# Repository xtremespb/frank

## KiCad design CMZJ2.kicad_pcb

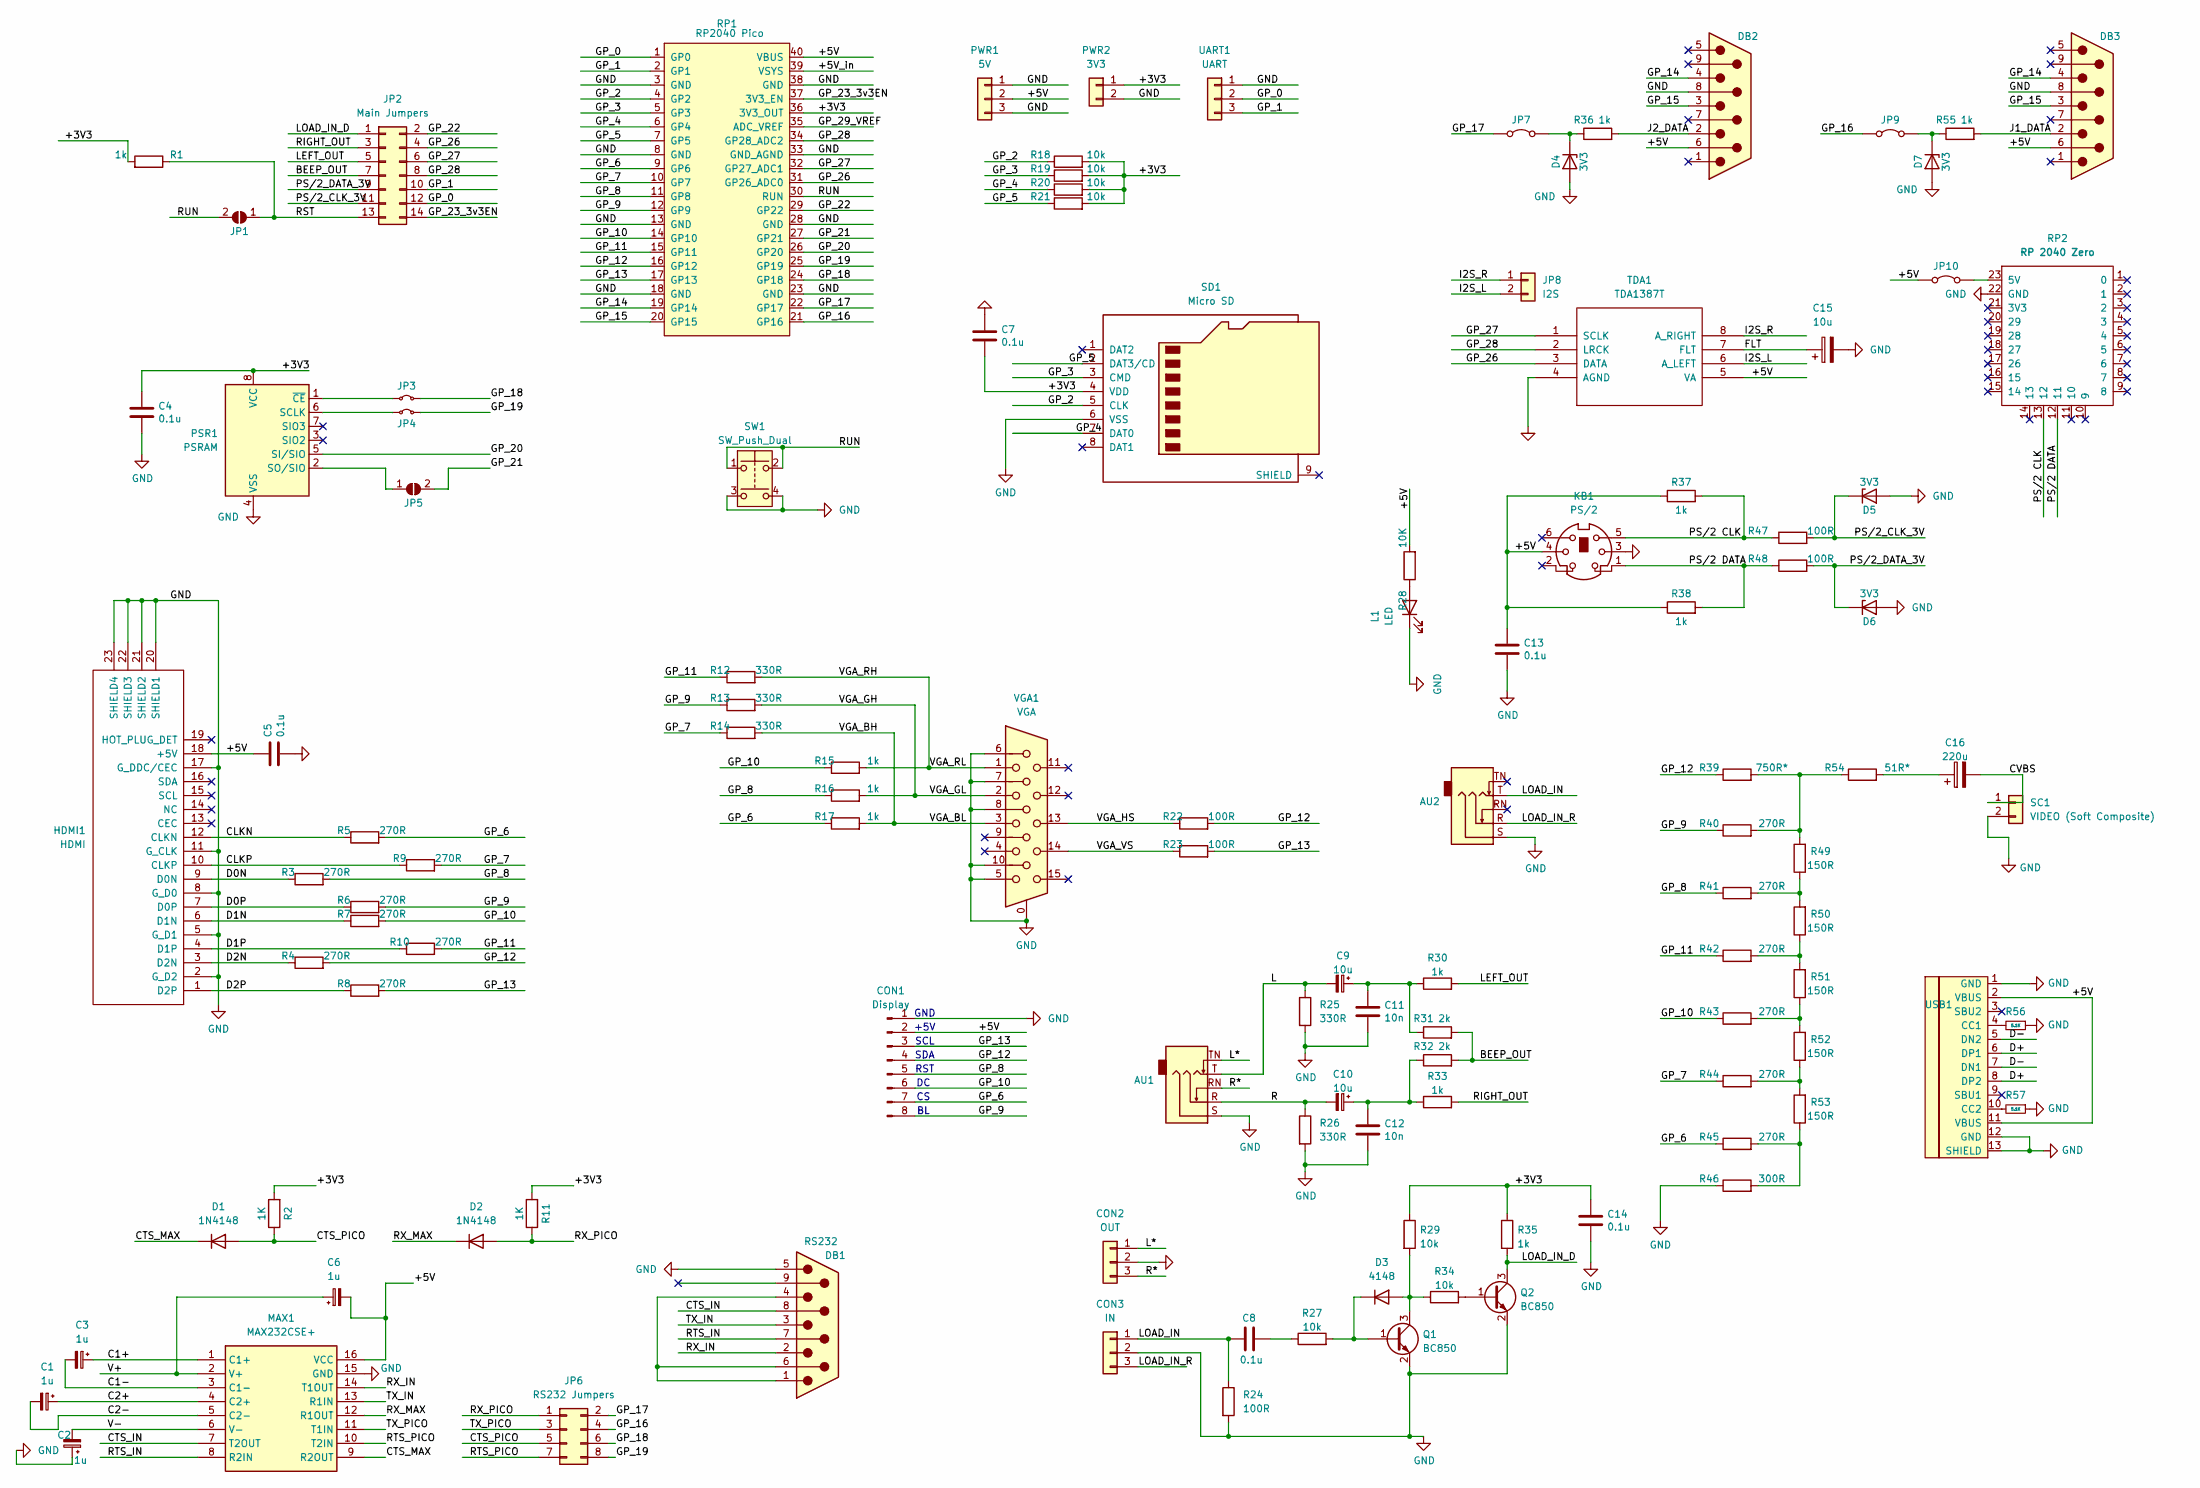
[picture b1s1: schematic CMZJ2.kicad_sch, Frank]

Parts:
AU1: AUDIO OUT; Medved_Jack_3.5mm_CUI_SJ1-3535NG_Horizontal
AU2: AUDIO IN; Medved_Jack_3.5mm_CUI_SJ1-3535NG_Horizontal
C1, C2, C3, C6: 1u; Medved_CP_Radial_D5.0mm_P2.50mm
C4, C5, C7, C8, C13, C14: 0.1u; C_0805_2012Metric_Pad1.18x1.45mm_HandSolder
C9, C10, C15: 10u; Medved_CP_Radial_D5.0mm_P2.50mm
C11, C12: 10n; C_0805_2012Metric_Pad1.18x1.45mm_HandSolder
C16: 220u; Medved_CP_Radial_D5.0mm_P2.50mm
CON1: Display; Medved_PinHeader_1x08_P2.54mm_Vertical
CON2: OUT; Medved_Pins_1x03_P2.54mm_Vertical_GM
CON3: IN; Medved_Pins_1x03_P2.54mm_Vertical_GM
D1, D2: 1N4148; R_0805_PLUS
D3: 4148; R_0805_PLUS
D4, D5, D6, D7: 3V3; R_0805_PLUS
DB1: RS232; DSUB-9_Joystick
DB2, DB3: Joystick; DSUB-9_Joystick
HDMI1: HDMI
JP1: JMP RUN; SolderJumper-2_P1.3mm_Open_RoundedPad1.0x1.5mm
JP2: Main Jumpers; Medved_PinHeader_2x07_P2.54mm_Vertical
JP3: GP18 Jumper; Medved_PinHeader_1x02_P2.54mm_Vertical_R
JP4: GP19 Jumper; Medved_PinHeader_1x02_P2.54mm_Vertical_R
JP5: JMP PSRAM; SolderJumper-2_P1.3mm_Open_RoundedPad1.0x1.5mm
JP6: RS232 Jumpers; Medved_PinHeader_2x04_P2.54mm_Vertical
JP7, JP9, JP10: RP ZERO +5V Jumper; Medved_PinHeader_1x02_P2.54mm_Vertical_R
JP8: I2S; Medved_PinHeader_1x02_P2.54mm_Vertical_NoLB
KB1: PS/2; Connector_Mini-DIN_Female_6Pin_2rows
L1: LED; LED_0805_2012Metric_Pad1.15x1.40mm_HandSolder
MAX1: MAX232CSE+; SOIC127P600X175-16N; Mouser Part Number 700-MAX232CSE
PSR1: PSRAM; SO-8_5.3x6.2mm_P1.27mm
PWR1: 5V; Medved_Pins_1x03_P2.54mm_Vertical
PWR2: 3V3; Medved_PinHeader_1x02_P2.54mm_Vertical
Q1, Q2: BC850; SOT-23_PLUS2
R1, R15, R16, R17, R30, R33, R35, R36, R37, R38, R55: 1k; R_0805_2012Metric_Pad1.20x1.40mm_HandSolder
R2, R11: 1K; R_0805_2012Metric_Pad1.20x1.40mm_HandSolder
R3, R4, R5, R6, R7, R8, R9, R10, R40, R41, R42, R43, R44, R45: 270R; R_0805_2012Metric_Pad1.20x1.40mm_HandSolder
R12, R13, R14, R25, R26: 330R; R_0805_2012Metric_Pad1.20x1.40mm_HandSolder
R18, R19, R20, R21, R27, R29, R34: 10k; R_0805_2012Metric_Pad1.20x1.40mm_HandSolder
R22, R23, R24, R47, R48: 100R; R_0805_2012Metric_Pad1.20x1.40mm_HandSolder
R28: 10K; R_0805_2012Metric_Pad1.20x1.40mm_HandSolder
R31, R32: 2k; R_0805_2012Metric_Pad1.20x1.40mm_HandSolder
R39: 750R*; R_0805_2012Metric_Pad1.20x1.40mm_HandSolder
R46: 300R; R_0805_2012Metric_Pad1.20x1.40mm_HandSolder
R49, R50, R51, R52, R53: 150R; R_0805_2012Metric_Pad1.20x1.40mm_HandSolder
R54: 51R*; R_0805_2012Metric_Pad1.20x1.40mm_HandSolder
R56, R57: 5.1K; R_0805_2012Metric_Pad1.20x1.40mm_HandSolder
RP1: RP2040 Pico; Raspberry_Pi_Pico_SMT_THT_MOD_2
RP2: RP 2040 Zero; rp2040-zero-tht
SC1: VIDEO (Soft Composite); AV_MOD_III-8.4-5
SD1: Micro SD; Medved_SD_Card
SW1: SW_Push_Dual; Button_SMD_3x3x2
TDA1: TDA1387T; SO-8_5.3x6.2mm_P1.27mm
UART1: UART; Medved_Pins_1x03_P2.54mm_Vertical
USB1: USB Type C; USB-TYPE-C-31-M-12_lib2; LCSC C165948
VGA1: VGA; Medved_DSUB-15-HD_Female_Horizontal

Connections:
/+3V3: C4.1, C7.2, C14.1, PSR1.8 (VCC), PWR2.1, R1.2, R2.2, R11.2, R18.2, R19.2, R20.2, R21.2, R29.1, R35.1, RP1.36 (3V3_OUT), SD1.4 (VDD)
/+5V: C5.1, C6.2, C13.1, CON1.2, DB2.6, DB3.6, HDMI1.18 (+5V), JP10.1 (A), KB1.4, MAX1.16 (VCC), PWR1.2, R28.2, R37.1, R38.1, RP1.40 (VBUS), TDA1.5 (VA), USB1.2 (VBUS), USB1.11 (VBUS)
/+5V_in: RP1.39 (VSYS)
/BEEP_OUT: JP2.7, R31.2, R32.2
/C1+: C3.1, MAX1.1 (C1+)
/C1-: C3.2, MAX1.3 (C1-)
/C2+: C1.1, MAX1.4 (C2+)
/C2-: C1.2, MAX1.5 (C2-)
/CLKN: HDMI1.12 (CLKN), R5.1
/CLKP: HDMI1.10 (CLKP), R9.1
/CTS_MAX: D1.1 (K), MAX1.9 (R2OUT)
/CTS_PICO: D1.2 (A), JP6.5, R2.1
/CVBS: C16.2, SC1.1
/D0N: HDMI1.9 (D0N), R3.1
/D0P: HDMI1.7 (D0P), R6.1
/D1N: HDMI1.6 (D1N), R7.1
/D1P: HDMI1.4 (D1P), R10.1
/D2N: HDMI1.3 (D2N), R4.1
/D2P: HDMI1.1 (D2P), R8.1
/D+: USB1.6 (DP1), USB1.8 (DP2)
/D-: USB1.5 (DN2), USB1.7 (DN1)
/FLT: C15.1, TDA1.7 (FLT)
/GP_0: JP2.12, RP1.1 (GP0), UART1.2
/GP_1: JP2.10, RP1.2 (GP1), UART1.3
/GP_2: R18.1, RP1.4 (GP2), SD1.5 (CLK)
/GP_3: R19.1, RP1.5 (GP3), SD1.3 (CMD)
/GP_4: R20.1, RP1.6 (GP4), SD1.7 (DAT0)
/GP_5: R21.1, RP1.7 (GP5), SD1.2 (DAT3/CD)
/GP_6: CON1.7, R5.2, R17.1, R45.1, RP1.9 (GP6)
/GP_7: R9.2, R14.1, R44.1, RP1.10 (GP7)
/GP_8: CON1.5, R3.2, R16.1, R41.1, RP1.11 (GP8)
/GP_9: CON1.8, R6.2, R13.1, R40.1, RP1.12 (GP9)
/GP_10: CON1.6, R7.2, R15.1, R43.1, RP1.14 (GP10)
/GP_11: R10.2, R12.1, R42.1, RP1.15 (GP11)
/GP_12: CON1.4, R4.2, R22.2, R39.1, RP1.16 (GP12)
/GP_13: CON1.3, R8.2, R23.2, RP1.17 (GP13)
/GP_14: DB2.4, DB3.4, RP1.19 (GP14)
/GP_15: DB2.3, DB3.3, RP1.20 (GP15)
/GP_16: JP6.4, JP9.1 (A), RP1.21 (GP16)
/GP_17: JP6.2, JP7.1 (A), RP1.22 (GP17)
/GP_18: JP3.2 (B), JP6.6, RP1.24 (GP18)
/GP_19: JP4.2 (B), JP6.8, RP1.25 (GP19)
/GP_20: PSR1.5 (SI/SIO), RP1.26 (GP20)
/GP_21: JP5.2 (B), RP1.27 (GP21)
/GP_22: JP2.2, RP1.29 (GP22)
/GP_23_3v3EN: JP2.14, RP1.37 (3V3_EN)
/GP_26: JP2.4, RP1.31 (GP26_ADC0), TDA1.3 (DATA)
/GP_27: JP2.6, RP1.32 (GP27_ADC1), TDA1.1 (SCLK)
/GP_28: JP2.8, RP1.34 (GP28_ADC2), TDA1.2 (LRCK)
/GP_29_VREF: RP1.35 (ADC_VREF)
/I2S_L: JP8.2, TDA1.6 (A_LEFT)
/I2S_R: JP8.1, TDA1.8 (A_RIGHT)
/J1_DATA: DB3.2, R55.2
/J2_DATA: DB2.2, R36.2
/L: AU1.T, C9.2, R25.1
/L*: AU1.TN, CON2.1
/LEFT_OUT: JP2.5, R30.2
/LOAD_IN: AU2.T, C8.1, CON3.1, R24.1
/LOAD_IN_D: JP2.1, Q2.3 (C), R35.2
/LOAD_IN_R: AU2.R, CON3.3
/PS/2 CLK: KB1.5, R37.2, R47.1, RP2.13 (12)
/PS/2 DATA: KB1.1, R38.2, R48.1, RP2.12 (11)
/PS/2_CLK_3V: D5.1 (K), JP2.11, R47.2
/PS/2_DATA_3V: D6.1 (K), JP2.9, R48.2
/R: AU1.R, C10.2, R26.1
/R*: AU1.RN, CON2.3
/RIGHT_OUT: JP2.3, R33.2
/RST: JP1.1 (A), JP2.13, R1.1
/RTS_PICO: JP6.7, MAX1.10 (T2IN)
/RUN: JP1.2 (B), RP1.30 (RUN), SW1.1, SW1.2
/RX_MAX: D2.1 (K), MAX1.12 (R1OUT)
/RX_PICO: D2.2 (A), JP6.1, R11.1
/TX_PICO: JP6.3, MAX1.11 (T1IN)
/V+: C6.1, MAX1.2 (V+)
/V-: C2.2, MAX1.6 (V-)
/VGA_BH: R14.2, R17.2, VGA1.3
/VGA_GH: R13.2, R16.2, VGA1.2
/VGA_HS: R22.1, VGA1.13
/VGA_RH: R12.2, R15.2, VGA1.1
/VGA_VS: R23.1, VGA1.14
GND: AU1.S, AU2.S, C2.1, C4.2, C5.2, C7.1, C11.2, C12.2, C13.2, C14.2, C15.2, CON1.1, CON2.2, CON3.2, D4.2 (A), D5.2 (A), D6.2 (A), D7.2 (A), DB1.5, DB2.8, DB3.8, HDMI1.2 (G_D2), HDMI1.5 (G_D1), HDMI1.8 (G_D0), HDMI1.11 (G_CLK), HDMI1.17 (G_DDC/CEC), HDMI1.20 (SHIELD1), HDMI1.21 (SHIELD2), HDMI1.22 (SHIELD3), HDMI1.23 (SHIELD4), KB1.3, L1.1 (K), MAX1.15 (GND), PSR1.4 (VSS), PWR1.1, PWR1.3, PWR2.2, Q1.2 (E), Q2.2 (E), R24.2, R25.2, R26.2, R46.1, R56.1, R57.1, RP1.3 (GND), RP1.8 (GND), RP1.13 (GND), RP1.18 (GND), RP1.23 (GND), RP1.28 (GND), RP1.33 (GND_AGND), RP1.38 (GND), RP2.22 (GND), SC1.2, SD1.6 (VSS), SW1.3, SW1.4, TDA1.4 (AGND), UART1.1, USB1.1 (GND), USB1.12 (GND), USB1.13 (SHIELD), VGA1.0, VGA1.5, VGA1.6, VGA1.7, VGA1.8, VGA1.10
unnamed: C8.2, R27.1
unnamed: C10.1, C12.1, R32.1, R33.1
unnamed: C9.1, C11.1, R30.1, R31.1
unnamed: C16.1, R54.2
unnamed: D3.2 (A), Q1.3 (C), R29.2, R34.1
unnamed: D3.1 (K), Q1.1 (B), R27.2
unnamed: D4.1 (K), JP7.2 (B), R36.1
unnamed: D7.1 (K), JP9.2 (B), R55.1
unnamed: DB1.1, DB1.4, DB1.6
unnamed: JP3.1 (A), PSR1.1 (~CE)
unnamed: JP4.1 (A), PSR1.6 (SCLK)
unnamed: JP5.1 (A), PSR1.2 (SO/SIO)
unnamed: JP10.2 (B), RP2.23 (5V)
unnamed: L1.2 (A), R28.1
unnamed: Q2.1 (B), R34.2
unnamed: R39.2, R40.2, R49.2, R54.1
unnamed: R41.2, R49.1, R50.2
unnamed: R42.2, R50.1, R51.2
unnamed: R43.2, R51.1, R52.2
unnamed: R44.2, R52.1, R53.2
unnamed: R45.2, R46.2, R53.1
unnamed: R56.2, USB1.4 (CC1)
unnamed: R57.2, USB1.10 (CC2)

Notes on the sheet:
+5V
SDA
GND
RST
SCL

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
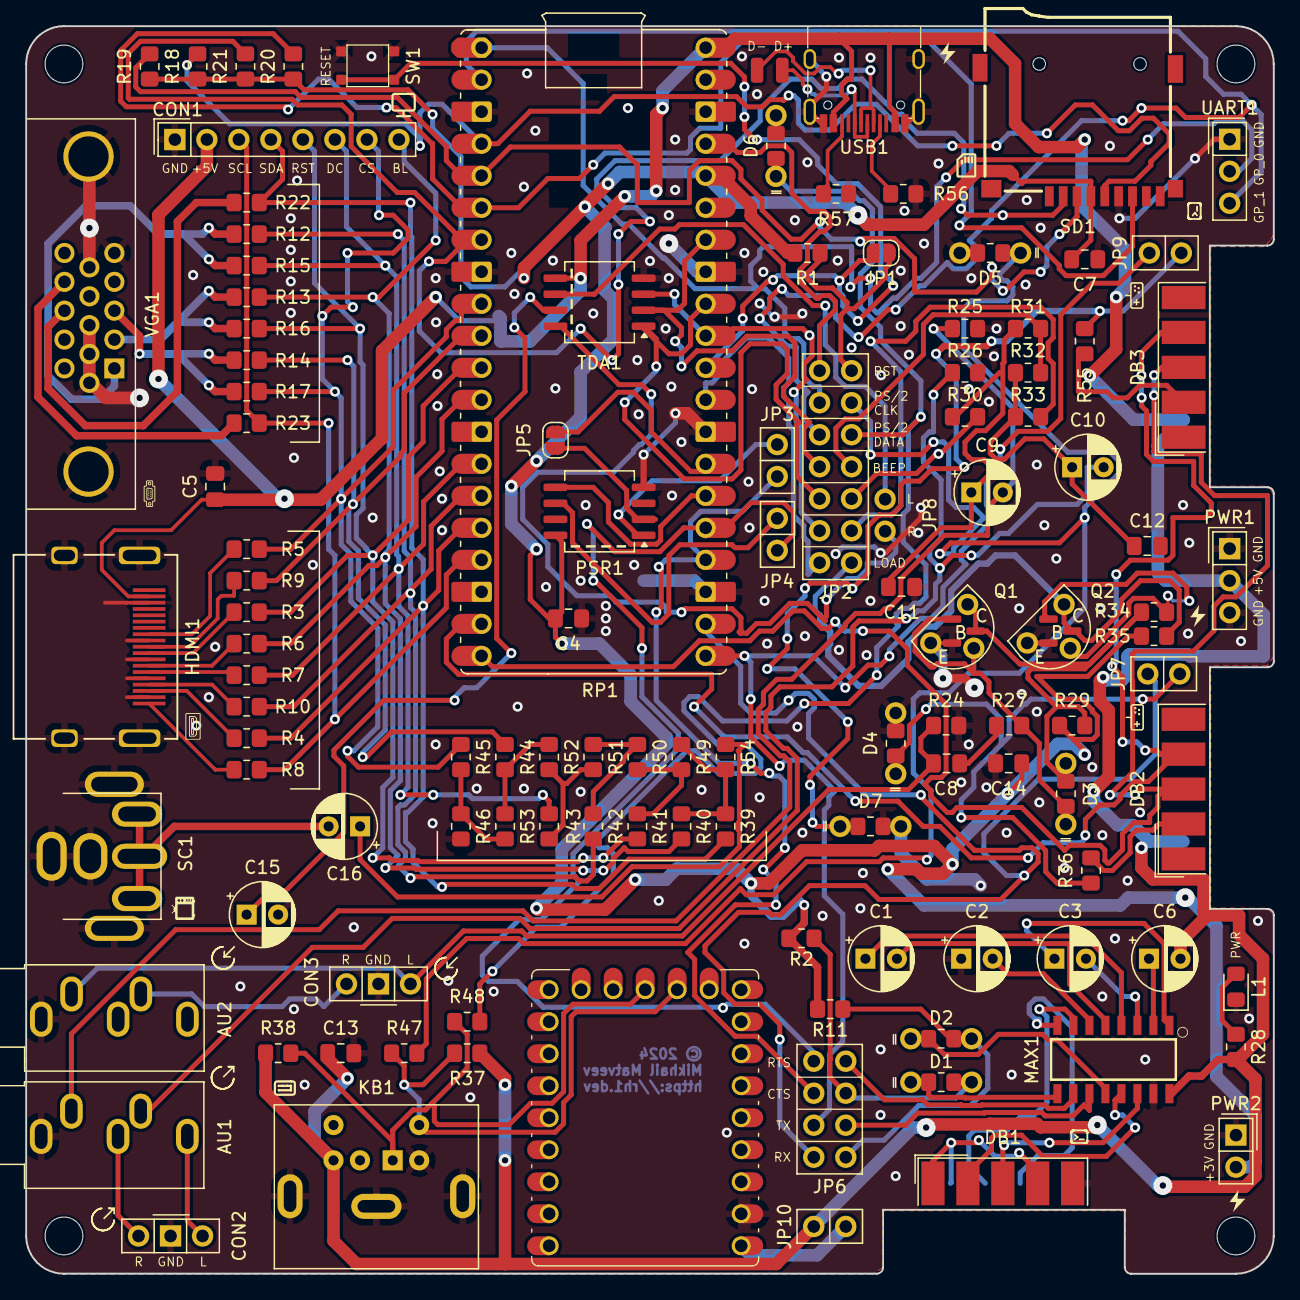
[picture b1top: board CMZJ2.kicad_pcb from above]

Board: 2 copper layers, 99.0 x 99.0 mm, 116 parts (0 on the bottom side), 106 nets.

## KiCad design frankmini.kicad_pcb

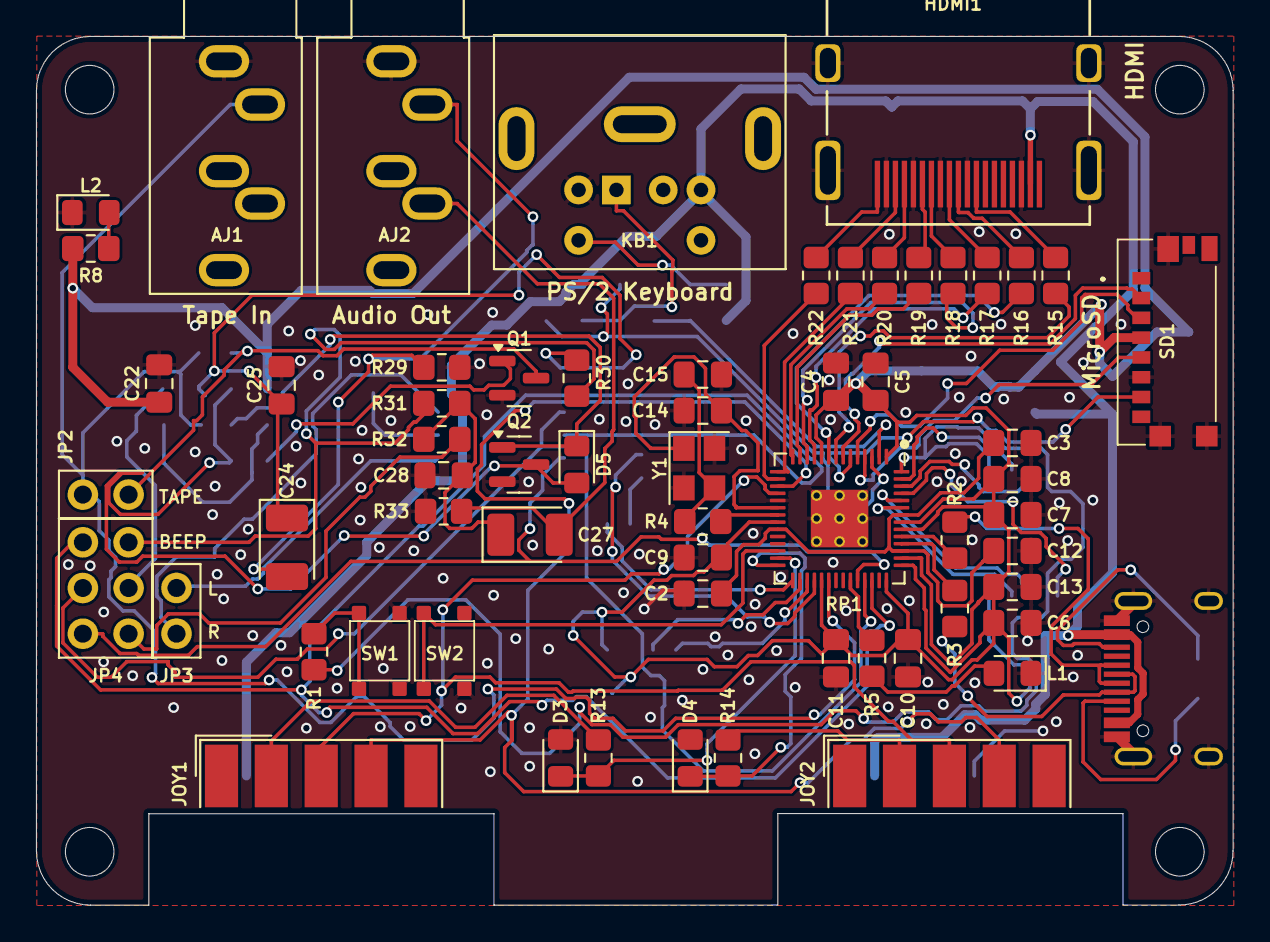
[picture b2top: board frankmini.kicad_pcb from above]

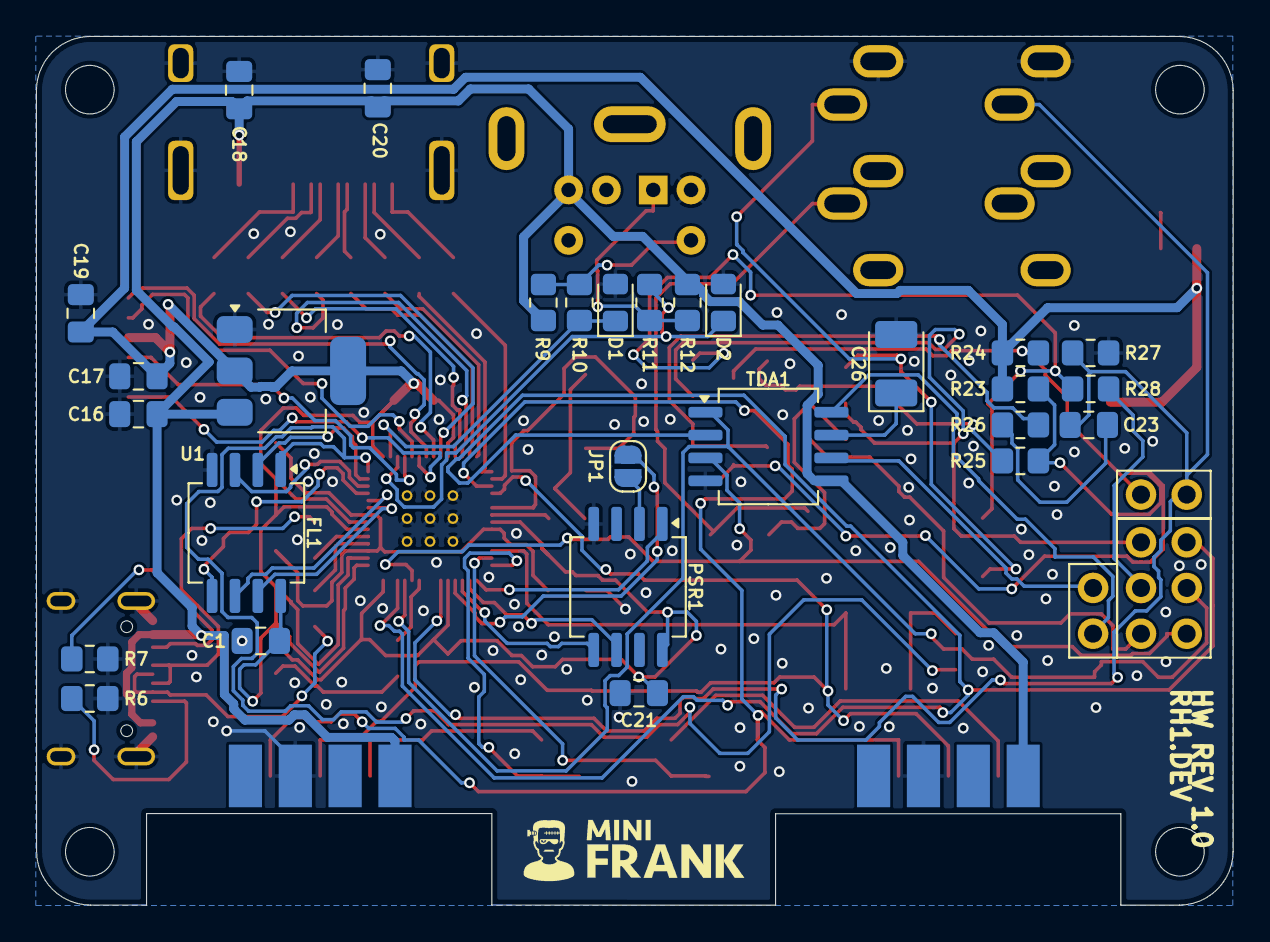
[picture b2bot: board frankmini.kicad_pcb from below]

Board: 2 copper layers, 66.5 x 48.3 mm, 94 parts (28 on the bottom side), 78 nets.

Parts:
AJ1: Audio IN; Jack_3.5mm
AJ2: Audio Out; Jack_3.5mm
C1, C2, C3, C4, C5, C6, C7, C8, C9, C10, C11, C18, C19, C20, C21, C22, C23: 100n; C_0805
C12, C13: 1u; C_0805
C14, C15: 15p; C_0805
C16, C17: 10u; C_0805
C24, C26, C27: 10u; CT_3528
C25, C28: 10n; C_0805
D1, D2, D3, D4: 3V3; D_0805
D5: 4148; D_0805
FL1: W25Q128JVS; SO_4x4
H1, H2, H3, H4: MountingHole; MountingHole_2.7
HDMI1: HDMI
JOY1, JOY2: Joystick; DSUB-9
JP1: JMP PSRAM; Jumper_S
JP2, JP3: I2S; PinHeader_1x02
JP4: Audio Jumpers; PinHeader_2x03
KB1: PS/2; Connector_Mini-DIN_Female_6Pin_2rows
L1: LED; L_0805
L2: GREEN; L_0805
PSR1: PSRAM; SO_4x4
Q1, Q2: BC850; Q_SOT-23
R1, R4, R5, R8, R9, R12, R13, R14, R24, R28, R32: 1K; R_0805
R2, R3: 27R; R_0805
R6, R7: 5.1K; R_0805
R10, R11, R27: 100R; R_0805
R15, R16, R17, R18, R19, R20, R21, R22: 270R; R_0805
R23, R25, R26: 10K; R_0805
R29, R33: 330R; R_0805
R30, R31: 2K; R_0805
RP1: RP2040; RP2040-QFN-56
SD1: 47571-0001; microsd
SW1: Flash Button; Button_SMD_3x3x2
SW2: Reset Button; Button_SMD_3x3x2
TDA1: TDA1387T; SO_4x4
U1: NCP1117-3.3_SOT223; SOT-223
USB1: USB Type C; USB-TYPE-C-31-M-12_lib2
Y1: 12 MHz; CR_3225

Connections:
+3V3: C1.1, C4.1, C5.1, C6.1, C7.1, C8.1, C9.1, C10.1, C11.1, C13.1, C17.1, C19.2, C21.1, C22.1, FL1.8 (VCC), PSR1.8 (VCC), R8.2, R23.1, R24.1, RP1.1 (IOVDD), RP1.10 (IOVDD), RP1.22 (IOVDD), RP1.33 (IOVDD), RP1.42 (IOVDD), RP1.43 (ADC_AVDD), RP1.44 (VREG_IN), RP1.48 (USB_VDD), RP1.49 (IOVDD), SD1.P4 (VDD), U1.2 (VO)
/AUDIO_B: JP4.6, RP1.40 (GPIO28_ADC2), TDA1.2 (LRCK)
/AUDIO_L: JP4.4, RP1.39 (GPIO27_ADC1), TDA1.1 (SCLK)
/AUDIO_R: JP4.2, RP1.38 (GPIO26_ADC0), TDA1.3 (DATA)
/Audio Out/BEEP_OUT: JP4.5, R30.2, R31.2
/Audio Out/FLT: C26.1, TDA1.7 (FLT)
/Audio Out/L: AJ2.T, C24.2, R29.1
/Audio Out/LEFT_OUT: JP4.3, R28.2
/Audio Out/LEFT_TDA: JP3.2, TDA1.6 (A_LEFT)
/Audio Out/R: AJ2.R, C27.2, R33.1
/Audio Out/RIGHT_OUT: JP4.1, R32.2
/Audio Out/RIGHT_TDA: JP3.1, TDA1.8 (A_RIGHT)
/D+: R2.1, USB1.6 (DP1), USB1.8 (DP2)
/D-: R3.1, USB1.5 (DN2), USB1.7 (DN1)
/GP1_DATA: D3.1 (K), R13.1, RP1.27 (GPIO16)
/GP2_DATA: D4.1 (K), R14.1, RP1.28 (GPIO17)
/GP_J3: JOY1.3, JOY2.3, RP1.18 (GPIO15)
/GP_J4: JOY1.4, JOY2.4, RP1.17 (GPIO14)
/HDMI_CLKN: R15.2, RP1.8 (GPIO6)
/HDMI_CLKP: R16.2, RP1.9 (GPIO7)
/HDMI_D0N: R17.2, RP1.11 (GPIO8)
/HDMI_D0P: R18.2, RP1.12 (GPIO9)
/HDMI_D1N: R19.2, RP1.13 (GPIO10)
/HDMI_D1P: R20.2, RP1.14 (GPIO11)
/HDMI_D2N: R21.2, RP1.15 (GPIO12)
/HDMI_D2P: R22.2, RP1.16 (GPIO13)
/LOAD_IN_D: AJ1.T, C23.1, JP2.2, R27.1, RP1.34 (GPIO22)
/PS2_CLK: D1.1 (K), R10.2, RP1.2 (GPIO0)
/PS2_DATA: D2.1 (K), R11.2, RP1.3 (GPIO1)
/PSR_CE: PSR1.1 (~CE), RP1.29 (GPIO18)
/PSR_SCLK: PSR1.6 (SCLK), RP1.30 (GPIO19)
/PSR_SISIO: PSR1.5 (SI/SIO), RP1.31 (GPIO20)
/PSR_SOSIO: JP1.2 (B), RP1.32 (GPIO21)
/RP2040/GPIO25: R5.2, RP1.37 (GPIO25)
/RP2040/QSPI_SCLK: FL1.6 (CLK), RP1.52 (QSPI_SCLK)
/RP2040/QSPI_SD0: FL1.5 (DI(IO0)), RP1.53 (QSPI_SD0)
/RP2040/QSPI_SD1: FL1.2 (DO(IO1)), RP1.55 (QSPI_SD1)
/RP2040/QSPI_SD2: FL1.3 (IO2), RP1.54 (QSPI_SD2)
/RP2040/QSPI_SD3: FL1.7 (IO3), RP1.51 (QSPI_SD3)
/RP2040/QSPI_SS: FL1.1 (~CS), R1.1, RP1.56 (QSPI_SS)
/RP2040/XIN: C14.1, RP1.20 (XIN), Y1.1
/RP2040/XOUT: R4.1, RP1.21 (XOUT)
/RP2040/~USB_BOOT: R1.2, SW1.3, SW1.4
/RUN: RP1.26 (RUN), SW2.3, SW2.4
/SD_CLK: RP1.4 (GPIO2), SD1.P5 (CLK)
/SD_CMD: RP1.5 (GPIO3), SD1.P3 (CMD)
/SD_DAT0: RP1.6 (GPIO4), SD1.P7 (DAT0)
/SD_DAT3: RP1.7 (GPIO5), SD1.P2 (CD/DAT3)
/Tape In/LOAD_IN_D: JP2.1, Q1.3 (C), R24.2
GND: AJ1.S, AJ2.S, C1.2, C2.2, C3.2, C4.2, C5.2, C6.2, C7.2, C8.2, C9.2, C10.2, C11.2, C12.2, C13.2, C14.2, C15.2, C16.2, C17.2, C18.2, C19.1, C20.2, C21.2, C22.2, C25.2, C26.2, C28.2, D1.2 (A), D2.2 (A), D3.2 (A), D4.2 (A), FL1.4 (GND), HDMI1.2 (G_D2), HDMI1.5 (G_D1), HDMI1.8 (G_D0), HDMI1.11 (G_CLK), HDMI1.17 (G_DDC/CEC), HDMI1.20 (SHIELD1), HDMI1.21 (SHIELD2), HDMI1.22 (SHIELD3), HDMI1.23 (SHIELD4), JOY1.8, JOY2.8, KB1.3, L1.1 (K), L2.1 (K), PSR1.4 (VSS), Q1.2 (E), Q2.2 (E), R6.1, R7.1, R27.2, R29.2, R33.2, RP1.19 (TESTEN), RP1.57 (GND), SD1.G1 (GND_1), SD1.G2 (GND_2), SD1.G3 (GND_3), SD1.P6 (VSS), SW1.1, SW1.2, SW2.1, SW2.2, TDA1.4 (AGND), U1.1 (GND), USB1.1 (GND), USB1.12 (GND), USB1.13 (SHIELD), Y1.2, Y1.4
unnamed: C15.1, R4.2, Y1.3
unnamed: C23.2, R26.1
unnamed: C24.1, C25.1, R28.1, R30.1
unnamed: C27.1, C28.1, R31.1, R32.1
unnamed: D5.2 (A), Q2.3 (C), R23.2, R25.1
unnamed: D5.1 (K), Q2.1 (B), R26.2
unnamed: HDMI1.12 (CLKN), R15.1
unnamed: HDMI1.10 (CLKP), R16.1
unnamed: HDMI1.9 (D0N), R17.1
unnamed: HDMI1.7 (D0P), R18.1
unnamed: HDMI1.6 (D1N), R19.1
unnamed: HDMI1.4 (D1P), R20.1
unnamed: HDMI1.3 (D2N), R21.1
unnamed: HDMI1.1 (D2P), R22.1
unnamed: JOY1.2, R13.2
unnamed: JOY2.2, R14.2
unnamed: JP1.1 (A), PSR1.2 (SO/SIO)
unnamed: KB1.1, R11.1, R12.2
unnamed: KB1.5, R9.2, R10.1
unnamed: L1.2 (A), R5.1
unnamed: L2.2 (A), R8.1
unnamed: Q1.1 (B), R25.2
unnamed: R3.2, RP1.46 (USB_DM)
unnamed: R2.2, RP1.47 (USB_DP)
unnamed: C2.1, C3.1, C12.1, RP1.23 (DVDD), RP1.45 (VREG_VOUT), RP1.50 (DVDD)
unnamed: R6.2, USB1.4 (CC1)
unnamed: R7.2, USB1.10 (CC2)
VBUS: C16.1, C18.1, C20.1, HDMI1.18 (+5V), JOY1.6, JOY2.6, KB1.4, R9.1, R12.1, TDA1.5 (VA), U1.3 (VI), USB1.2 (VBUS), USB1.11 (VBUS)

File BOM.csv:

"Reference","Value","Datasheet","Footprint","Qty","DNP"
"AJ1","Audio IN","~","LIBS:Jack_3.5mm","1",""
"AJ2","Audio Out","~","LIBS:Jack_3.5mm","1",""
"C1,C2,C3,C4,C5,C6,C7,C8,C9,C10,C11,C18,C19,C20,C21,C22,C23","100n","~","LIBS:C_0805","17",""
"C12,C13","1u","~","LIBS:C_0805","2",""
"C14,C15","15p","~","LIBS:C_0805","2",""
"C16,C17","10u","~","LIBS:C_0805","2",""
"C24,C26,C27","10u (tantal)","~","-- mixed values --","3",""
"C25,C28","10n","~","LIBS:C_0805","2",""
"D1,D2,D3,D4","3V3","~","LIBS:D_0805","4",""
"D5","1N4148","~","LIBS:D_0805","1",""
"FL1","W25Q128JVSIQ","http://www.winbond.com/resource-files/w25q128jv_dtr%20revc%2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","LIBS:SO_4x4","1",""
"HDMI1","HDMI","","LIBS:HDMI","1",""
"JOY1,JOY2","Joystick","~","LIBS:DSUB-9","2",""
"JP1","JMP PSRAM","~","LIBS:Jumper_S","1",""
"JP2","TAPE IN","~","LIBS:PinHeader_1x02","1",""
"JP3","I2S","~","LIBS:PinHeader_1x02","1",""
"JP4","Audio Jumpers","~","LIBS:PinHeader_2x03","1",""
"KB1","PS/2","http://service.powerdynamics.com/ec/Catalog17/Section%2011.pdf","LIBS:Connector_Mini-DIN_Female_6Pin_2rows","1",""
"L1","LED","~","LIBS:L_0805","1",""
"L2","GREEN","~","LIBS:L_0805","1",""
"PSR1","PSRAM","https://www.espressif.com/sites/default/files/documentation/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","LIBS:SO_4x4","1",""
"Q1,Q2","BC850","http://www.infineon.com/dgdl/Infineon-BC847SERIES_BC848SERIE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","LIBS:Q_SOT-23","2",""
"R1,R4,R5,R8,R9,R12,R13,R14,R24,R28,R32","1K","~","LIBS:R_0805","11",""
"R2,R3","27R","~","LIBS:R_0805","2",""
"R6,R7","5.1K","","LIBS:R_0805","2",""
"R10,R11,R27","100R","~","LIBS:R_0805","3",""
"R15,R16,R17,R18,R19,R20,R21,R22","270R","~","LIBS:R_0805","8",""
"R23,R25,R26","10K","~","LIBS:R_0805","3",""
"R29,R33","330R","~","LIBS:R_0805","2",""
"R30,R31","2K","~","LIBS:R_0805","2",""
"RP1","RP2040","","LIBS:RP2040-QFN-56","1",""
"SD1","47571-0001","https://componentsearchengine.com/Datasheets/2/47571-0001.pdf","LIBS:microsd","1",""
"SW1","Flash Button","~","LIBS:Button_SMD_3x3x2","1",""
"SW2","Reset Button","~","LIBS:Button_SMD_3x3x2","1",""
"TDA1","TDA1387T","","LIBS:SO_4x4","1",""
"U1","NCP1117-3.3_SOT223","http://www.onsemi.com/pub_link/Collateral/NCP1117-D.PDF","LIBS:SOT-223","1",""
"USB1","USB Type C","","LIBS:USB-TYPE-C-31-M-12_lib2","1",""
"Y1","12 MHz","~","LIBS:CR_3225","1",""

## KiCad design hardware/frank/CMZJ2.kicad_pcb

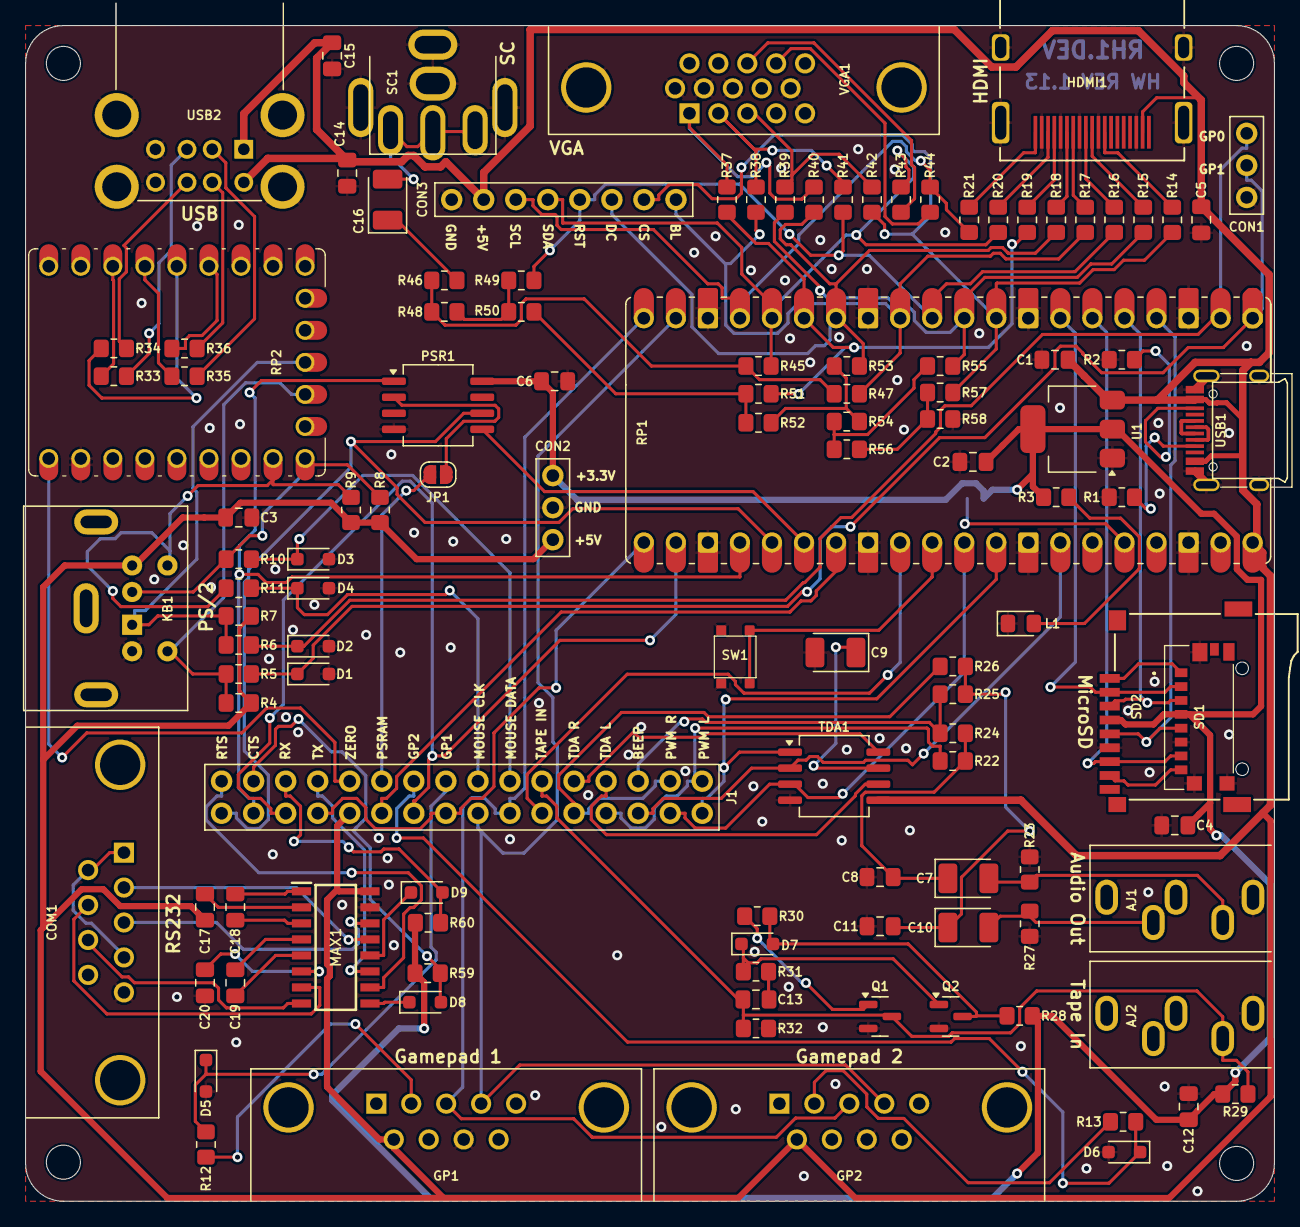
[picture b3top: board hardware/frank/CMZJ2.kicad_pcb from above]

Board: 2 copper layers, 99.0 x 93.2 mm, 122 parts (1 on the bottom side), 112 nets.

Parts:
AJ1, AJ2: SJ1-353XNG; Jack (3.5mm)
C1, C2, C14, C15: 10u; Capacitor (0805)
C3, C4, C5, C6, C12, C13: 100n; Capacitor (0805)
C7, C9, C10: 10u; Capacitor (3528, tantalum, polar)
C8, C11: 10n; Capacitor (0805)
C16: 220u; Capacitor (3528, tantalum, polar)
C17, C18, C19, C20: 1u; Capacitor (0805)
COM1: D-SUB 9 Male; D-SUB (9 pin, male, top mount)
CON1, CON2: Pin Header 1x03; Pin Header (1x03)
CON3: Pin Header 1x08; Pin Header (1x08)
D1, D2, D3, D4, D5, D6: 3V3; Diode (SOD-323)
D7, D8, D9: 1N4148; Diode (SOD-323)
GP1, GP2: D-SUB 9 Male; D-SUB (9 pin, male, top mount)
H1, H2, H3, H4: Hole 2.7mm; Mounting Hole (2.7mm)
HDMI1: DC3RX19JA2; HDMI (female)
J1: Pin Header 2x18; Pin Header (2x16)
JP1, JP2: Jumper (Solder); Jumper (solder)
KB1: MDC-036; MiniDIN (6 Pin, female)
L1: Green; LED (0805)
MAX1: MAX232CSE+; SOIC127P600X175-16N
PSR1: ESP-PSRAM32; SOIC-8
Q1, Q2: BC850; SOT-23
R1, R2: 5.1K; Resistor (0805)
R3, R4, R7, R8, R9, R12, R13, R22, R26, R29, R40, R41, R42, R59, R60: 1K; Resistor (0805)
R5, R6, R10, R11, R32, R43, R44: 100R; Resistor (0805)
R14, R15, R16, R17, R18, R19, R20, R21, R47, R49, R51, R53, R55, R57: 270R; Resistor (0805)
R23, R27, R37, R38, R39: 330R; Resistor (0805)
R24, R25: 2K; Resistor (0805)
R28, R30, R31: 10K; Resistor (0805)
R33, R34, R35, R36: 22R; Resistor (0805)
R45: 750R; Resistor (0805)
R46: 51R; Resistor (0805)
R48, R50, R52, R54, R56: 150R; Resistor (0805)
R58: 300R; Resistor (0805)
RP1: Rasberry Pi Pico; Raspberry Pi Pico
RP2: RP2040-Zero; Raspberry Pi Zero
SC1: RCA-103; RCA
SD1: 0475710001; MicroSD (SMD, short)
SD2: 104031-0811; MicroSD (SMD, long)
SW1: KLS7-TS3302; Button (SMD, 3x3mm)
TDA1: TDA1387T; SOIC-8
U1: NCP1117 3.3; SOT-223
USB1: USB4215; USB Type C
USB2: SS-52100-004; USB Type A (stacked)
VGA1: D-SUB 15 Female; D-SUB (15 pin, female)

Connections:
+3V3: C2.1, C4.2, C6.1, C12.1, CON2.1, JP2.2 (B), PSR1.8 (VCC), R3.2, R28.1, R29.1, R59.2, R60.2, SD1.P4 (VDD), SD2.4 (VDD), U1.2 (VO)
/A_OUTB: J1.5, R24.2, R25.2
/A_OUTL: J1.1, J1.8, R22.2
/A_OUTR: J1.3, J1.10, R26.2
/A_TDAL: J1.7, TDA1.6 (A_LEFT)
/A_TDAR: J1.9, TDA1.8 (A_RIGHT)
/Audio Out/L: AJ1.T, C7.2, R23.1
/Audio Out/R: AJ1.R, C10.2, R27.1
/Composite/CVBS: C16.2, SC1.1
/GP1_DATA: D5.1 (K), J1.17, R12.1
/GP2_DATA: D6.1 (K), J1.19, R13.1
/GPIO0: CON1.2, D1.1 (K), R5.2, RP1.1 (GPIO0)
/GPIO1: CON1.3, D2.1 (K), R6.2, RP1.2 (GPIO1)
/GPIO2: RP1.4 (GPIO2), SD1.P5 (CLK), SD2.5 (CLK)
/GPIO3: RP1.5 (GPIO3), SD1.P3 (CMD), SD2.3 (CMD)
/GPIO4: RP1.6 (GPIO4), SD1.P7 (DAT0), SD2.7 (DAT0)
/GPIO5: RP1.7 (GPIO5), SD1.P2 (CD/DAT3), SD2.2 (DAT3/CD)
/GPIO6: CON3.7, R14.2, R42.1, R57.1, RP1.9 (GPIO6)
/GPIO7: R15.2, R39.1, R55.1, RP1.10 (GPIO7)
/GPIO8: CON3.5, R16.2, R41.1, R49.1, RP1.11 (GPIO8)
/GPIO9: CON3.8, R17.2, R38.1, R47.1, RP1.12 (GPIO9)
/GPIO10: CON3.6, R18.2, R40.1, R53.1, RP1.14 (GPIO10)
/GPIO11: R19.2, R37.1, R51.1, RP1.15 (GPIO11)
/GPIO12: CON3.4, R20.2, R43.2, R45.1, RP1.16 (GPIO12)
/GPIO13: CON3.3, R21.2, R44.2, RP1.17 (GPIO13)
/GPIO14: GP1.4, GP2.4, J1.16, RP1.19 (GPIO14)
/GPIO15: GP1.3, GP2.3, J1.14, RP1.20 (GPIO15)
/GPIO16: J1.18, J1.26, RP1.21 (GPIO16)
/GPIO17: J1.20, J1.28, RP1.22 (GPIO17)
/GPIO18: J1.30, PSR1.1 (~CE), RP1.24 (GPIO18)
/GPIO19: J1.32, PSR1.6 (SCLK), RP1.25 (GPIO19)
/GPIO20: PSR1.5 (SI/SIO), RP1.26 (GPIO20)
/GPIO21: J1.22, RP1.27 (GPIO21)
/GPIO22: J1.12, RP1.29 (GPIO22)
/GPIO26: J1.4, RP1.31 (GPIO26_ADC0), TDA1.3 (DATA)
/GPIO27: J1.2, RP1.32 (GPIO27_ADC1), TDA1.1 (SCLK)
/GPIO28: J1.6, RP1.34 (GPIO28_ADC2), TDA1.2 (LRCK)
/KB_CLK: KB1.5, R4.2, R5.1, RP2.13 (12)
/KB_DATA: KB1.1, R6.1, R7.2, RP2.12 (11)
/LOAD_IN_D: AJ2.T, C13.1, J1.11, Q1.3 (C), R29.2, R32.1
/MS_CLK: KB1.6, R9.2, R11.1, RP2.16 (15)
/MS_CLK_3V: D4.1 (K), J1.15, R11.2
/MS_DATA: KB1.2, R8.2, R10.1, RP2.15 (14)
/MS_DATA_3V: D3.1 (K), J1.13, R10.2
/Micro SD/DAT1: SD1.P8 (DAT1), SD2.8 (DAT1)
/Micro SD/DAT2: SD1.P1 (DAT2), SD2.1 (DAT2)
/PSR_SOSIO: J1.21, JP1.2 (B)
/Power/D+: USB1.6 (DP1), USB1.8 (DP2)
/Power/D-: USB1.5 (DN2), USB1.7 (DN1)
/RS232/C1+: C18.2, MAX1.1 (C1+)
/RS232/C1-: C18.1, MAX1.3 (C1-)
/RS232/C2+: C19.2, MAX1.4 (C2+)
/RS232/C2-: C19.1, MAX1.5 (C2-)
/RS232/CTS_IN: COM1.7, MAX1.7 (T2OUT)
/RS232/CTS_MAX: D8.1 (K), MAX1.9 (R2OUT)
/RS232/RTS_IN: COM1.8, MAX1.8 (R2IN)
/RS232/RX_IN: COM1.3, MAX1.14 (T1OUT)
/RS232/RX_MAX: D9.1 (K), MAX1.12 (R1OUT)
/RS232/TX_IN: COM1.2, MAX1.13 (R1IN)
/RS232/V+: C17.1, MAX1.2 (V+)
/RS232/V-: C20.1, MAX1.6 (V-)
/RS232_CTS: D8.2 (A), J1.29, R59.1
/RS232_RTS: J1.31, MAX1.10 (T2IN)
/RS232_RX: D9.2 (A), J1.27, R60.1
/RS232_TX: J1.25, MAX1.11 (T1IN)
/RUN: RP1.30 (RUN), SW1.3, SW1.4
/USB_D1M: R35.1, RP2.4 (3)
/USB_D1P: R33.1, RP2.3 (2)
/USB_D2M: R36.1, RP2.6 (5)
/USB_D2P: R34.1, RP2.5 (4)
/ZERO_VBUS: J1.23, RP2.23 (5V)
GND: AJ1.S, AJ2.S, C1.2, C2.2, C3.2, C4.1, C5.2, C6.2, C8.2, C9.2, C11.2, C12.2, C14.2, C15.2, C20.2, COM1.5, CON1.1, CON2.2, CON3.1, D1.2 (A), D2.2 (A), D3.2 (A), D4.2 (A), D5.2 (A), D6.2 (A), GP1.8, GP2.8, HDMI1.2 (G_D2), HDMI1.5 (G_D1), HDMI1.8 (G_D0), HDMI1.11 (G_CLK), HDMI1.17 (G_DDC/CEC), HDMI1.20 (SHIELD1), HDMI1.21 (SHIELD2), HDMI1.22 (SHIELD3), HDMI1.23 (SHIELD4), KB1.3, L1.1 (K), MAX1.15 (GND), PSR1.4 (VSS), Q1.2 (E), Q2.2 (E), R1.1, R2.1, R23.2, R27.2, R32.2, R58.1, RP1.3 (GND), RP1.8 (GND), RP1.13 (GND), RP1.18 (GND), RP1.23 (GND), RP1.28 (GND), RP1.33 (AGND), RP1.38 (GND), RP2.22 (GND), SC1.2, SD1.G1 (GND_1), SD1.G2 (GND_2), SD1.G3 (GND_3), SD1.P6 (VSS), SD2.6 (VSS), SW1.1, SW1.2, TDA1.4 (AGND), U1.1 (GND), USB1.1 (GND), USB1.12 (GND), USB1.13 (SHIELD), USB2.4 (GND1), USB2.8 (GND2), USB2.9 (Shield), VGA1.0, VGA1.5, VGA1.6, VGA1.7, VGA1.8, VGA1.10
unnamed: C7.1, C8.1, R22.1, R24.1
unnamed: C10.1, C11.1, R25.1, R26.1
unnamed: C13.2, R31.1
unnamed: C16.1, R46.2
unnamed: COM1.1, COM1.4, COM1.6
unnamed: D7.2 (A), Q2.3 (C), R28.2, R30.1
unnamed: D7.1 (K), Q2.1 (B), R31.2
unnamed: GP1.2, R12.2
unnamed: GP2.2, R13.2
unnamed: HDMI1.12 (CLKN), R14.1
unnamed: HDMI1.10 (CLKP), R15.1
unnamed: HDMI1.9 (D0N), R16.1
unnamed: HDMI1.7 (D0P), R17.1
unnamed: HDMI1.6 (D1N), R18.1
unnamed: HDMI1.4 (D1P), R19.1
unnamed: HDMI1.3 (D2N), R20.1
unnamed: HDMI1.1 (D2P), R21.1
unnamed: JP1.1 (A), PSR1.2 (SO/SIO)
unnamed: JP2.1 (A), RP1.36 (3V3)
unnamed: L1.2 (A), R3.1
unnamed: Q1.1 (B), R30.2
unnamed: R37.2, R40.2, VGA1.1
unnamed: R38.2, R41.2, VGA1.2
unnamed: R39.2, R42.2, VGA1.3
unnamed: R43.1, VGA1.13
unnamed: R44.1, VGA1.14
unnamed: R45.2, R46.1, R47.2, R48.2
unnamed: R48.1, R49.2, R50.2
unnamed: R50.1, R51.2, R52.2
unnamed: R52.1, R53.2, R54.2
unnamed: R54.1, R55.2, R56.2
unnamed: R56.1, R57.2, R58.2
unnamed: C9.1, TDA1.7 (FLT)
unnamed: R1.2, USB1.4 (CC1)
unnamed: R2.2, USB1.10 (CC2)
unnamed: R33.2, USB2.3 (D1+)
unnamed: R35.2, USB2.2 (D1-)
unnamed: R34.2, USB2.7 (D2+)
unnamed: R36.2, USB2.6 (D2-)
VBUS: C1.1, C3.1, C5.1, C14.1, C15.1, C17.2, CON2.3, CON3.2, GP1.6, GP2.6, HDMI1.18 (+5V), J1.24, KB1.4, MAX1.16 (VCC), R4.1, R7.1, R8.1, R9.1, RP1.40 (VBUS), TDA1.5 (VA), U1.3 (VI), USB1.2 (VBUS), USB1.11 (VBUS), USB2.1 (VBUS1), USB2.5 (VBUS2)

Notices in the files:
CMZJ2.kicad_pcb:
© 2024
